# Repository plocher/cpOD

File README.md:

# cpOD
## License: Creative Commons Attribution-NonCommercial-ShareAlike

cpOD
Pulse Transformer based Occupancy Detector

Inspired by Dr Bruce Chubb's DCCOD, as well as work done by MFS and MRCS

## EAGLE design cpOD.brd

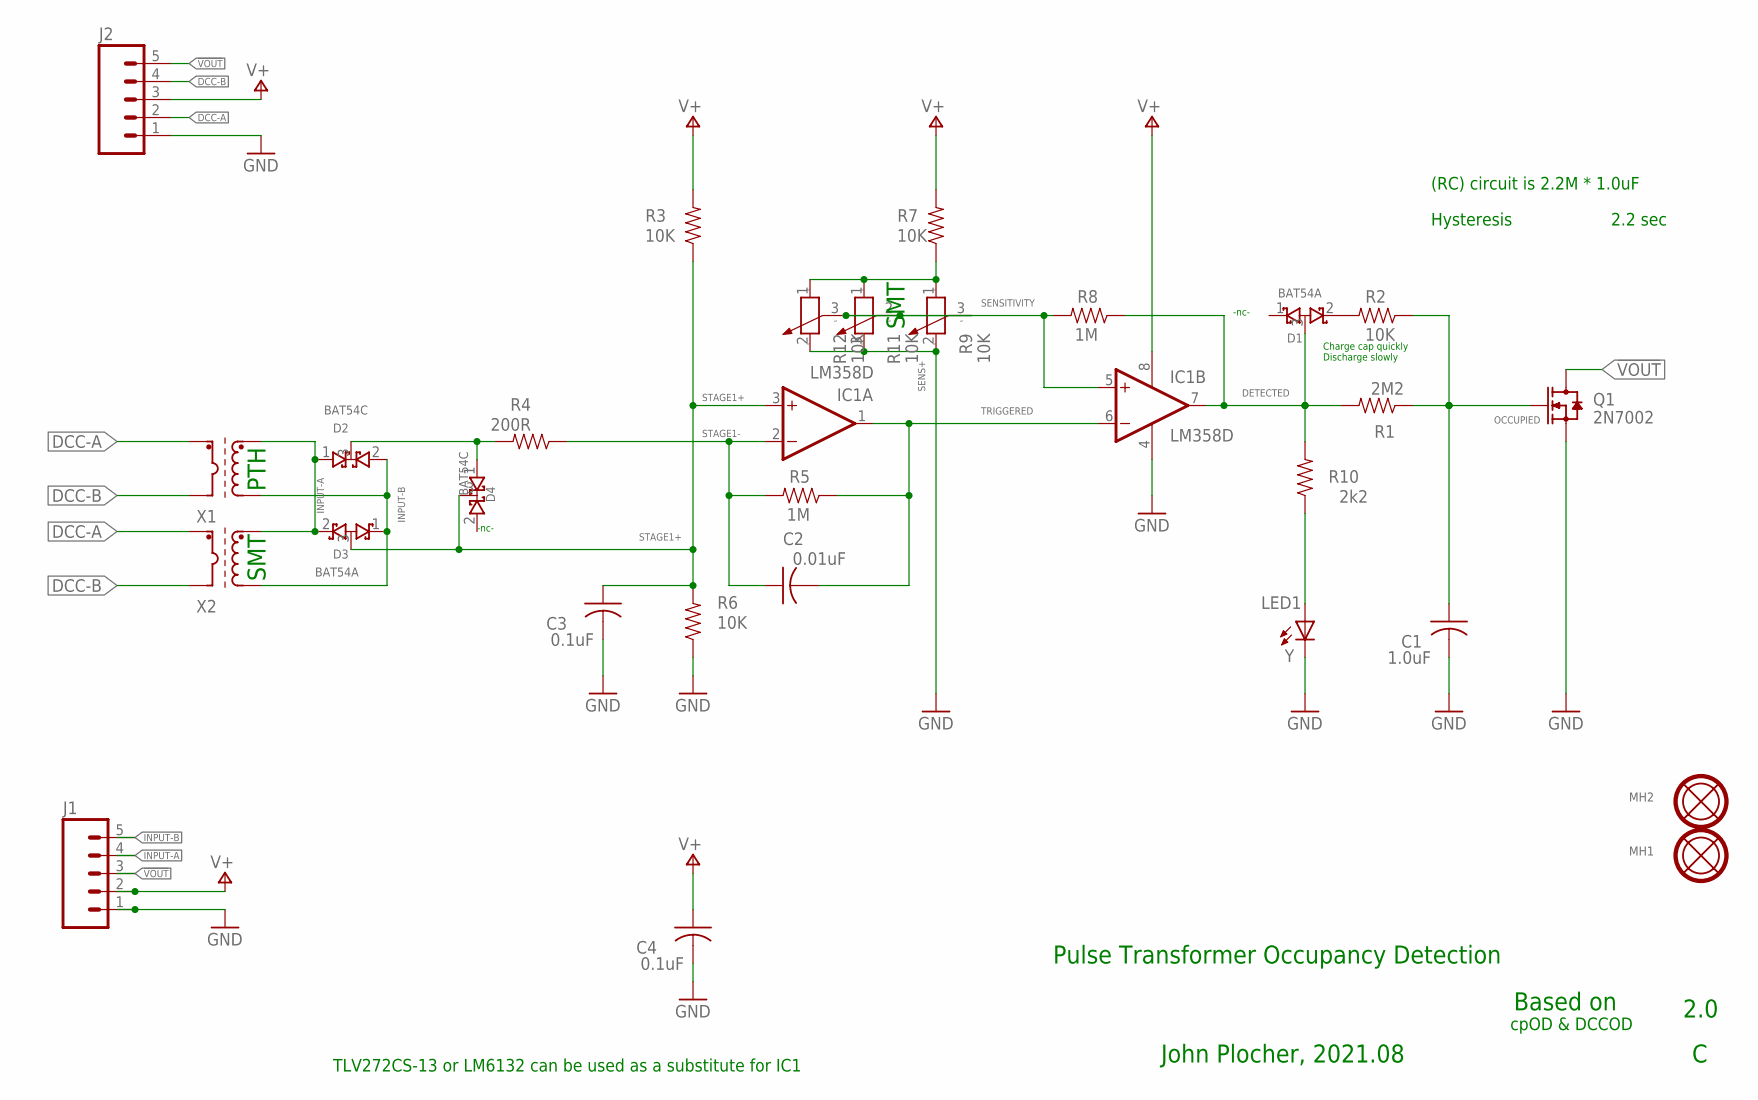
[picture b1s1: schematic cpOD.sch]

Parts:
C1: 1.0uF; 0603-CAP
C2: 0.01uF; 0603-CAP
C3, C4: 0.1uF; 0603-CAP
D1, D3: BAT54A; SOT23
D2, D4: BAT54C; SOT23
IC1: LM358D; SO-8
J1: CONNECTOR-M05PTH; 1X05
J2: CONNECTOR-M051.56; KK-156-5
LED1: Y; 0603-LED
MH1, MH2: MOUNTINGHOLEL; MOUNTINGHOLE-L
Q1: 2N7002; SOT23
R1: 2M2; 0603-RES
R2, R3, R6, R7: 10K; 0603-RES
R4: 200R; 0603-RES
R5, R8: 1M; 0603-RES
R9: 10K; ST-4
R10: 2k2; 0603-RES
R11: 10K; PT-10S
R12: 10K; TC33X
X1: PULSE-TRANSFORMERPTH-RB; TH-T4B
X2: PULSE-TRANSFORMERM; M5300

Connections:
!VOUT: J1.3, J2.5, Q1.3 (D)
DCC-A: J2.2, X1.P2 (DCC-B), X2.8 (DCC-B)
DCC-B: J2.4, X1.P1 (DCC-A), X2.7 (DCC-A)
DETECTED: D1.3 (COM), IC1.7 (OUT), R1.2, R8.1, R10.2
FAST-RISE: D1.2 (C2), R2.2
GND: C1.2, C3.2, C4.2, IC1.4 (V-), J1.1, J2.1, LED1.C, Q1.2 (S), R6.1, R9.2 (E), R11.3 (E), R12.2 (E)
INPUT-A: D2.1 (A1), D3.2 (C2), J1.4, X1.S2 (OUT-B), X2.1 (OUT-B)
INPUT-B: D2.2 (A2), D3.1 (C1), J1.5, X1.S1 (OUT-A), X2.3 (OUT-A)
INPUT-NEGATIVE: D2.3 (COM), D4.1 (A1), R4.2
unnamed: LED1.A, R10.1
OCCUPIED: C1.1, Q1.1 (G), R1.1, R2.1
SENS+: R7.1, R9.1 (A), R11.1 (A), R12.1 (A)
SENSITIVITY: IC1.5 (+IN), R8.2, R9.3 (S), R11.2 (S), R12.3 (S)
STAGE1+: C3.1, D3.3 (COM), D4.3 (COM), IC1.3 (+IN), R3.1, R6.2
STAGE1-: C2.1, IC1.2 (-IN), R4.1, R5.2
TRIGGERED: C2.2, IC1.1 (OUT), IC1.6 (-IN), R5.1
V+: C4.1, IC1.8 (V+), J1.2, J2.3, R3.2, R7.2

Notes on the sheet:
Hysteresis
2.2 sec
Based on
TLV272CS-13 or LM6132 can be used as a substitute for IC1
Pulse Transformer Occupancy Detection
Charge cap quickly Discharge slowly
-nc-
(RC) circuit is 2.2M * 1.0uF
2.0
John Plocher, 2021.08
cpOD & DCCOD
PTH
SMT

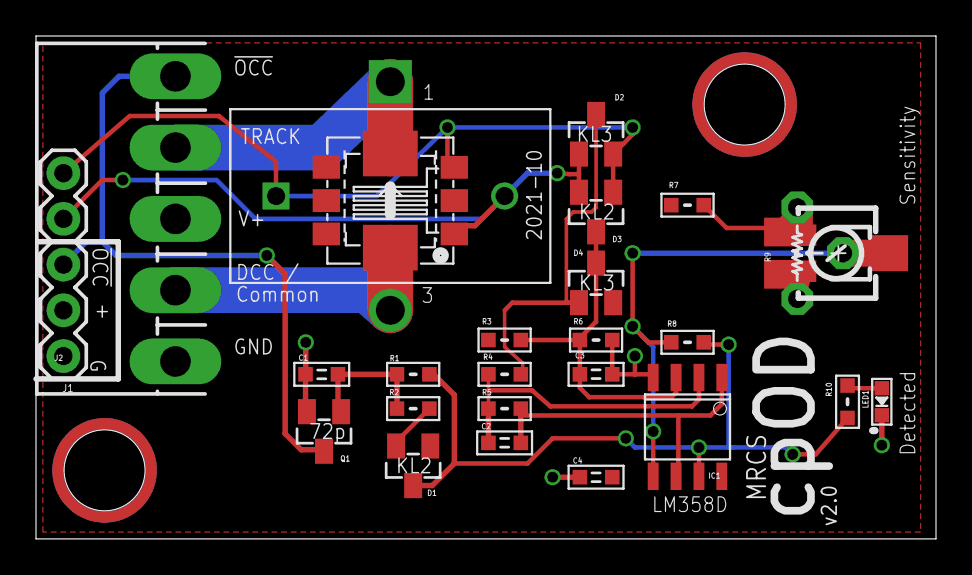
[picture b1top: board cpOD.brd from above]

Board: 2 copper layers, 50.0 x 27.9 mm, 29 parts (0 on the bottom side), 17 nets.

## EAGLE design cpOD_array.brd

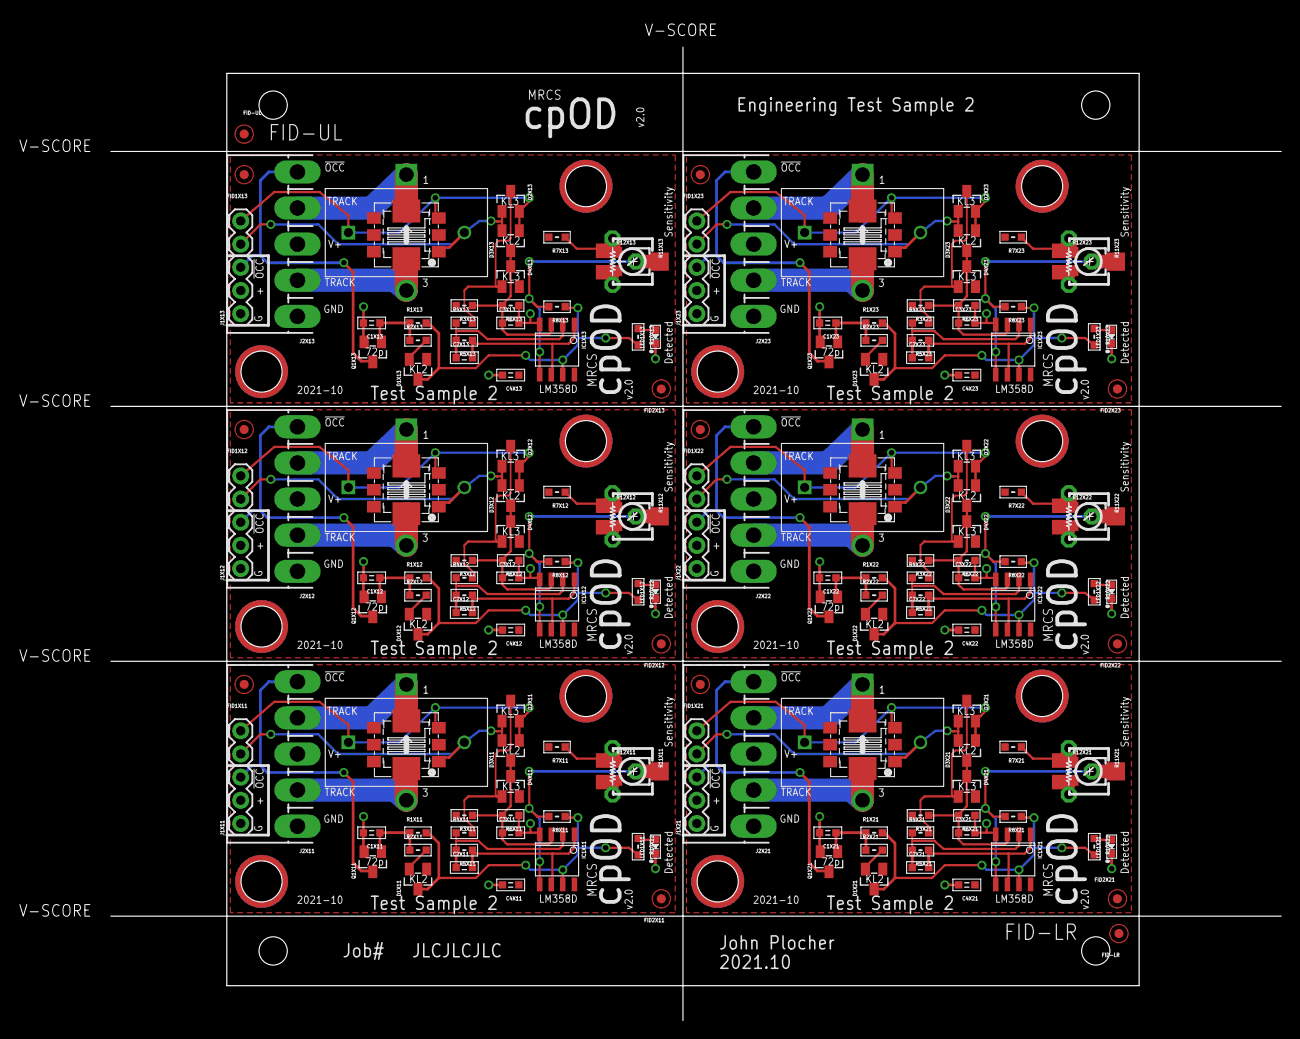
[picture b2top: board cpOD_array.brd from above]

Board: 2 copper layers, 138.4 x 109.8 mm, 189 parts (0 on the bottom side), 102 nets.

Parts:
C1X11, C1X12, C1X13, C1X21, C1X22, C1X23: 1.0uF; 0603-CAP
C2X11, C2X12, C2X13, C2X21, C2X22, C2X23: 0.01uF; 0603-CAP
C3X11, C3X12, C3X13, C3X21, C3X22, C3X23, C4X11, C4X12, C4X13, C4X21, C4X22, C4X23: 0.1uF; 0603-CAP
D1X11, D1X12, D1X13, D1X21, D1X22, D1X23, D3X11, D3X12, D3X13, D3X21, D3X22, D3X23: BAT54A; SOT23
D2X11, D2X12, D2X13, D2X21, D2X22, D2X23, D4X11, D4X12, D4X13, D4X21, D4X22, D4X23: BAT54C; SOT23
FID1X11, FID1X12, FID1X13, FID1X21, FID1X22, FID1X23, FID2X11, FID2X12, FID2X13, FID2X21, FID2X22, FID2X23: FIDUCIAL; FIDUCIAL_1MM
FID-LR: FIDUCIAL_1MM
FID-UL: FIDUCIAL_1MM
IC1X11, IC1X12, IC1X13, IC1X21, IC1X22, IC1X23: LM358D; SO-8
J1X11, J1X12, J1X13, J1X21, J1X22, J1X23: 1X05
J2X11, J2X12, J2X13, J2X21, J2X22, J2X23: KK-156-5
LED1X11, LED1X12, LED1X13, LED1X21, LED1X22, LED1X23: Y; 0603-LED
Q1X11, Q1X12, Q1X13, Q1X21, Q1X22, Q1X23: 2N7002; SOT23
R1X11, R1X12, R1X13, R1X21, R1X22, R1X23: 2M2; 0603-RES
R2X11, R2X12, R2X13, R2X21, R2X22, R2X23, R3X11, R3X12, R3X13, R3X21, R3X22, R3X23, R6X11, R6X12, R6X13, R6X21, R6X22, R6X23, R7X11, R7X12, R7X13, R7X21, R7X22, R7X23: 10K; 0603-RES
R4X11, R4X12, R4X13, R4X21, R4X22, R4X23: 200R; 0603-RES
R5X11, R5X12, R5X13, R5X21, R5X22, R5X23, R8X11, R8X12, R8X13, R8X21, R8X22, R8X23: 1M; 0603-RES
R9X11, R9X12, R9X13, R9X21, R9X22, R9X23: 10K; ST-4
R10X11, R10X12, R10X13, R10X21, R10X22, R10X23: 2k2; 0603-RES
R11X11, R11X12, R11X13, R11X21, R11X22, R11X23: 10K; PT-10S
R12X11, R12X12, R12X13, R12X21, R12X22, R12X23: 10K; TC33X
U$1X11, U$1X12, U$1X13, U$1X21, U$1X22, U$1X23, U$2X11, U$2X12, U$2X13, U$2X21, U$2X22, U$2X23: MOUNTINGHOLEL; MOUNTINGHOLE-L
X1X11, X1X12, X1X13, X1X21, X1X22, X1X23: TH-T4B
X2X1: BOARD-10X10-3X2-PANEL
X2X11, X2X12, X2X13, X2X21, X2X22, X2X23: M5300

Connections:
!VOUTX11: J1X11.3, J2X11.5, Q1X11.3
!VOUTX12: J1X12.3, J2X12.5, Q1X12.3
!VOUTX13: J1X13.3, J2X13.5, Q1X13.3
!VOUTX21: J1X21.3, J2X21.5, Q1X21.3
!VOUTX22: J1X22.3, J2X22.5, Q1X22.3
!VOUTX23: J1X23.3, J2X23.5, Q1X23.3
DCC-AX11: J2X11.2, X1X11.P2, X2X11.8
DCC-AX12: J2X12.2, X1X12.P2, X2X12.8
DCC-AX13: J2X13.2, X1X13.P2, X2X13.8
DCC-AX21: J2X21.2, X1X21.P2, X2X21.8
DCC-AX22: J2X22.2, X1X22.P2, X2X22.8
DCC-AX23: J2X23.2, X1X23.P2, X2X23.8
DCC-BX11: J2X11.4, X1X11.P1, X2X11.7
DCC-BX12: J2X12.4, X1X12.P1, X2X12.7
DCC-BX13: J2X13.4, X1X13.P1, X2X13.7
DCC-BX21: J2X21.4, X1X21.P1, X2X21.7
DCC-BX22: J2X22.4, X1X22.P1, X2X22.7
DCC-BX23: J2X23.4, X1X23.P1, X2X23.7
DETECTEDX11: D1X11.3, IC1X11.7, R1X11.2, R8X11.1, R10X11.2
DETECTEDX12: D1X12.3, IC1X12.7, R1X12.2, R8X12.1, R10X12.2
DETECTEDX13: D1X13.3, IC1X13.7, R1X13.2, R8X13.1, R10X13.2
DETECTEDX21: D1X21.3, IC1X21.7, R1X21.2, R8X21.1, R10X21.2
DETECTEDX22: D1X22.3, IC1X22.7, R1X22.2, R8X22.1, R10X22.2
DETECTEDX23: D1X23.3, IC1X23.7, R1X23.2, R8X23.1, R10X23.2
FAST-RISEX11: D1X11.2, R2X11.2
FAST-RISEX12: D1X12.2, R2X12.2
FAST-RISEX13: D1X13.2, R2X13.2
FAST-RISEX21: D1X21.2, R2X21.2
FAST-RISEX22: D1X22.2, R2X22.2
FAST-RISEX23: D1X23.2, R2X23.2
GNDX11: C1X11.2, C3X11.2, C4X11.2, IC1X11.4, J1X11.1, J2X11.1, LED1X11.C, Q1X11.2, R6X11.1, R9X11.2, R11X11.3, R12X11.2
GNDX12: C1X12.2, C3X12.2, C4X12.2, IC1X12.4, J1X12.1, J2X12.1, LED1X12.C, Q1X12.2, R6X12.1, R9X12.2, R11X12.3, R12X12.2
GNDX13: C1X13.2, C3X13.2, C4X13.2, IC1X13.4, J1X13.1, J2X13.1, LED1X13.C, Q1X13.2, R6X13.1, R9X13.2, R11X13.3, R12X13.2
GNDX21: C1X21.2, C3X21.2, C4X21.2, IC1X21.4, J1X21.1, J2X21.1, LED1X21.C, Q1X21.2, R6X21.1, R9X21.2, R11X21.3, R12X21.2
GNDX22: C1X22.2, C3X22.2, C4X22.2, IC1X22.4, J1X22.1, J2X22.1, LED1X22.C, Q1X22.2, R6X22.1, R9X22.2, R11X22.3, R12X22.2
GNDX23: C1X23.2, C3X23.2, C4X23.2, IC1X23.4, J1X23.1, J2X23.1, LED1X23.C, Q1X23.2, R6X23.1, R9X23.2, R11X23.3, R12X23.2
INPUT-AX11: D2X11.1, D3X11.2, J1X11.4, X1X11.S2, X2X11.1
INPUT-AX12: D2X12.1, D3X12.2, J1X12.4, X1X12.S2, X2X12.1
INPUT-AX13: D2X13.1, D3X13.2, J1X13.4, X1X13.S2, X2X13.1
INPUT-AX21: D2X21.1, D3X21.2, J1X21.4, X1X21.S2, X2X21.1
INPUT-AX22: D2X22.1, D3X22.2, J1X22.4, X1X22.S2, X2X22.1
INPUT-AX23: D2X23.1, D3X23.2, J1X23.4, X1X23.S2, X2X23.1
INPUT-BX11: D2X11.2, D3X11.1, J1X11.5, X1X11.S1, X2X11.3
INPUT-BX12: D2X12.2, D3X12.1, J1X12.5, X1X12.S1, X2X12.3
INPUT-BX13: D2X13.2, D3X13.1, J1X13.5, X1X13.S1, X2X13.3
INPUT-BX21: D2X21.2, D3X21.1, J1X21.5, X1X21.S1, X2X21.3
INPUT-BX22: D2X22.2, D3X22.1, J1X22.5, X1X22.S1, X2X22.3
INPUT-BX23: D2X23.2, D3X23.1, J1X23.5, X1X23.S1, X2X23.3
INPUT-NEGATIVEX11: D2X11.3, D4X11.1, R4X11.2
INPUT-NEGATIVEX12: D2X12.3, D4X12.1, R4X12.2
INPUT-NEGATIVEX13: D2X13.3, D4X13.1, R4X13.2
INPUT-NEGATIVEX21: D2X21.3, D4X21.1, R4X21.2
INPUT-NEGATIVEX22: D2X22.3, D4X22.1, R4X22.2
INPUT-NEGATIVEX23: D2X23.3, D4X23.1, R4X23.2
unnamed: LED1X11.A, R10X11.1
unnamed: LED1X12.A, R10X12.1
unnamed: LED1X13.A, R10X13.1
unnamed: LED1X21.A, R10X21.1
unnamed: LED1X22.A, R10X22.1
unnamed: LED1X23.A, R10X23.1
OCCUPIEDX11: C1X11.1, Q1X11.1, R1X11.1, R2X11.1
OCCUPIEDX12: C1X12.1, Q1X12.1, R1X12.1, R2X12.1
OCCUPIEDX13: C1X13.1, Q1X13.1, R1X13.1, R2X13.1
OCCUPIEDX21: C1X21.1, Q1X21.1, R1X21.1, R2X21.1
OCCUPIEDX22: C1X22.1, Q1X22.1, R1X22.1, R2X22.1
OCCUPIEDX23: C1X23.1, Q1X23.1, R1X23.1, R2X23.1
SENS+X11: R7X11.1, R9X11.1, R11X11.1, R12X11.1
SENS+X12: R7X12.1, R9X12.1, R11X12.1, R12X12.1
SENS+X13: R7X13.1, R9X13.1, R11X13.1, R12X13.1
SENS+X21: R7X21.1, R9X21.1, R11X21.1, R12X21.1
SENS+X22: R7X22.1, R9X22.1, R11X22.1, R12X22.1
SENS+X23: R7X23.1, R9X23.1, R11X23.1, R12X23.1
SENSITIVITYX11: IC1X11.5, R8X11.2, R9X11.3, R11X11.2, R12X11.3
SENSITIVITYX12: IC1X12.5, R8X12.2, R9X12.3, R11X12.2, R12X12.3
SENSITIVITYX13: IC1X13.5, R8X13.2, R9X13.3, R11X13.2, R12X13.3
SENSITIVITYX21: IC1X21.5, R8X21.2, R9X21.3, R11X21.2, R12X21.3
SENSITIVITYX22: IC1X22.5, R8X22.2, R9X22.3, R11X22.2, R12X22.3
SENSITIVITYX23: IC1X23.5, R8X23.2, R9X23.3, R11X23.2, R12X23.3
STAGE1+X11: C3X11.1, D3X11.3, D4X11.3, IC1X11.3, R3X11.1, R6X11.2
STAGE1+X12: C3X12.1, D3X12.3, D4X12.3, IC1X12.3, R3X12.1, R6X12.2
STAGE1+X13: C3X13.1, D3X13.3, D4X13.3, IC1X13.3, R3X13.1, R6X13.2
STAGE1+X21: C3X21.1, D3X21.3, D4X21.3, IC1X21.3, R3X21.1, R6X21.2
STAGE1+X22: C3X22.1, D3X22.3, D4X22.3, IC1X22.3, R3X22.1, R6X22.2
STAGE1+X23: C3X23.1, D3X23.3, D4X23.3, IC1X23.3, R3X23.1, R6X23.2
STAGE1-X11: C2X11.1, IC1X11.2, R4X11.1, R5X11.2
STAGE1-X12: C2X12.1, IC1X12.2, R4X12.1, R5X12.2
STAGE1-X13: C2X13.1, IC1X13.2, R4X13.1, R5X13.2
STAGE1-X21: C2X21.1, IC1X21.2, R4X21.1, R5X21.2
STAGE1-X22: C2X22.1, IC1X22.2, R4X22.1, R5X22.2
STAGE1-X23: C2X23.1, IC1X23.2, R4X23.1, R5X23.2
TRIGGEREDX11: C2X11.2, IC1X11.1, IC1X11.6, R5X11.1
TRIGGEREDX12: C2X12.2, IC1X12.1, IC1X12.6, R5X12.1
TRIGGEREDX13: C2X13.2, IC1X13.1, IC1X13.6, R5X13.1
TRIGGEREDX21: C2X21.2, IC1X21.1, IC1X21.6, R5X21.1
TRIGGEREDX22: C2X22.2, IC1X22.1, IC1X22.6, R5X22.1
TRIGGEREDX23: C2X23.2, IC1X23.1, IC1X23.6, R5X23.1
V+X11: C4X11.1, IC1X11.8, J1X11.2, J2X11.3, R3X11.2, R7X11.2
V+X12: C4X12.1, IC1X12.8, J1X12.2, J2X12.3, R3X12.2, R7X12.2
V+X13: C4X13.1, IC1X13.8, J1X13.2, J2X13.3, R3X13.2, R7X13.2
V+X21: C4X21.1, IC1X21.8, J1X21.2, J2X21.3, R3X21.2, R7X21.2
V+X22: C4X22.1, IC1X22.8, J1X22.2, J2X22.3, R3X22.2, R7X22.2
V+X23: C4X23.1, IC1X23.8, J1X23.2, J2X23.3, R3X23.2, R7X23.2

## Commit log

2021-09-01 Initial version
2021-10-02 initial
2021-10-02 2.0B-WIP
2021-10-03 Version 1.1
2021-10-03 LED1 shorted, D2/3 reversed
2021-10-04 panelized
2021-10-16 Version 2.0
